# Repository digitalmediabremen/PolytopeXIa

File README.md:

# Polytope XIa

see *developer blog* at https://digitalmediabremen.github.io/PolytopeXIa/

## how to convert a java sketches to processing

navigate to sketch folder ( i.e `./PolytopeXIa/sketches` ) and run shell script `convert-java-to-processing.sh` with the first argument pointing to the java sketch source file:

```
./convert-java-to-processing.sh ../src/de/hfkbremen/polytopexia/sketches/LaserBeamLogo.java
```

note that you might need to manually add libraries in the processing editor ( e.g `import teilchen.*;` or `import.gewebe.*;` ( from https://github.com/dennisppaul/gewebe ) ).

## See osc.schema.md for a list of commands

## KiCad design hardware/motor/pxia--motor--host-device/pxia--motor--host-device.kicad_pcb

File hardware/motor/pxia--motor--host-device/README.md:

# Polytope XIa / hardware / motor / host-device

( TTL>RS485>RJ45 ) 

- via MAX490

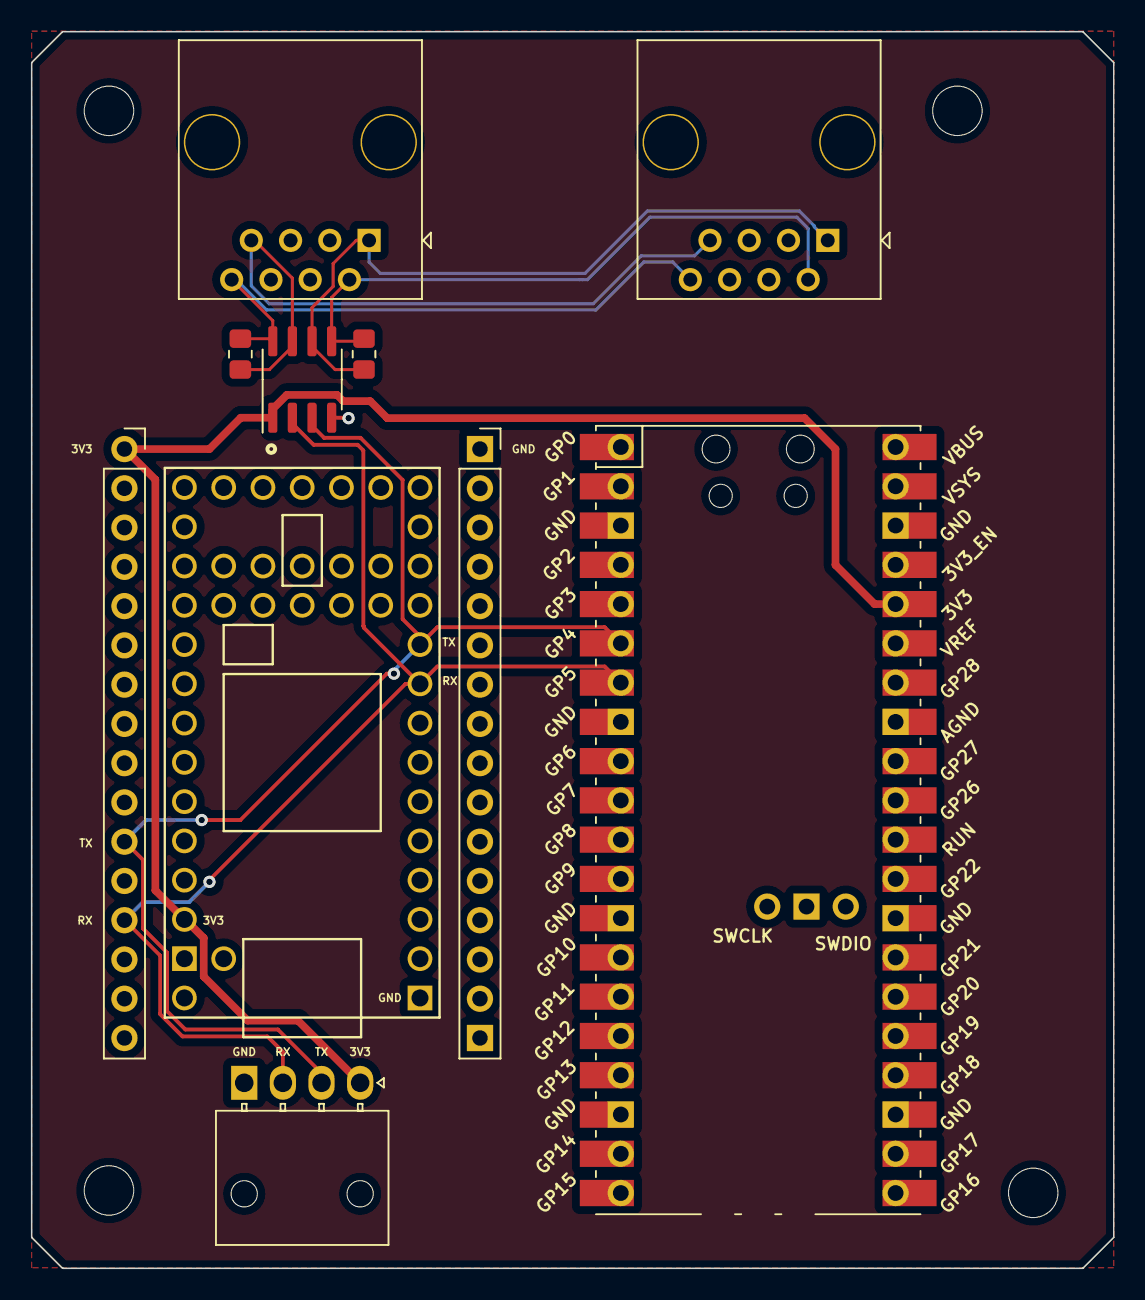
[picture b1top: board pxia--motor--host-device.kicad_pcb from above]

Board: 2 copper layers, 70.0 x 80.0 mm, 14 parts (0 on the bottom side), 8 nets.

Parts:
H1, H2, H3, H4: M3; MountingHole_3.2mm_M3
J1, J5: RJ45; RJ45_OST_PJ012-8P8CX_Vertical
J2: Lolin D32 Pro 2.0.0 (ESP32) PIN17–32; PinSocket_1x16_P2.54mm_Vertical
J3: GENERIC_UART; Molex_Nano-Fit_105313-xx04_1x04_P2.50mm_Horizontal
J4: Lolin D32 Pro 2.0.0 (ESP32) PIN01–16; PinSocket_1x16_P2.54mm_Vertical
R1, R2: 120R; R_0805_2012Metric_Pad1.20x1.40mm_HandSolder
U1: Teensy4.0; Teensy40
U2: max3490eesa+T; SOIC-8_3.9x4.9mm_P1.27mm
U3: PicoW; RPi_PicoW_SMD_TH

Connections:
+3V3: J3.1, J4.1, U1.31 (3V3), U2.1 (VCC), U3.36 (3V3)
/MCU_RX: J3.3, J4.13, U1.9 (7_RX2_OUT1A), U2.2 (RO), U3.7 (GPIO5)
/MCU_TX: J3.2, J4.11, U1.10 (8_TX2_IN1), U2.3 (DI), U3.6 (GPIO4)
/RX+: J1.2, J5.2, R1.1, U2.5 (Y)
/RX-: J1.1, J5.1, R1.2, U2.6 (Z)
/TX+: J1.8, J5.8, R2.1, U2.8 (A)
/TX-: J1.7, J5.7, R2.2, U2.7 (B)
GND: J2.1, J2.16, J3.4, U1.1 (GND), U1.17 (GND), U1.32 (AGND), U2.4 (GND), U3.3 (GND), U3.8 (GND), U3.13 (GND), U3.18 (GND), U3.23 (GND), U3.28 (GND), U3.33 (AGND), U3.38 (GND), U3.42 (GND)

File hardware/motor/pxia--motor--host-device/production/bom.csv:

Designator,Footprint,Quantity,Value,LCSC Part #
"H1, H2, H3, H4",MountingHole_3.2mm_M3,4,M3,DNF
"J1, J5",RJ45_OST_PJ012-8P8CX_Vertical,2,RJ45,C305983
J2,PinSocket_1x16_P2.54mm_Vertical,1,Lolin D32 Pro 2.0.0 (ESP32) PIN17–32,DNF
J3,Molex_Nano-Fit_105313-xx04_1x04_P2.50mm_Horizontal,1,GENERIC_UART,DNF
J4,PinSocket_1x16_P2.54mm_Vertical,1,Lolin D32 Pro 2.0.0 (ESP32) PIN01–16,DNF
"R1, R2",R_0805_2012Metric_Pad1.20x1.40mm_HandSolder,2,120R,C114244
U1,Teensy40,1,Teensy4.0,DNF
U2,SOIC-8_3.9x4.9mm_P1.27mm,1,max3490eesa+T,C23404
U3,RPi_PicoW_SMD_TH,1,PicoW,DNF

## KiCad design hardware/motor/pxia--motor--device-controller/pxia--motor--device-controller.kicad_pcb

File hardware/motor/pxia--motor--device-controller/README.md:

# Polytope XIa / hardware / motor / device-controller

( RJ45+PWR>JSTPHD )

## RJ45 connector @JLCPCB

### horizontal

- MFR.Part # [1-406525-1](https://jlcpcb.com/partdetail/TeConnectivity-1_4065251/C125066)

### vertical

- MFR.Part # [5555799-1](https://jlcpcb.com/partdetail/TeConnectivity-55557991/C305983) #black #plastic #vertical **FAV**
- MFR.Part # [5557969-1](https://jlcpcb.com/partdetail/TeConnectivity-55579691/C305977) #silver #metal #vertical

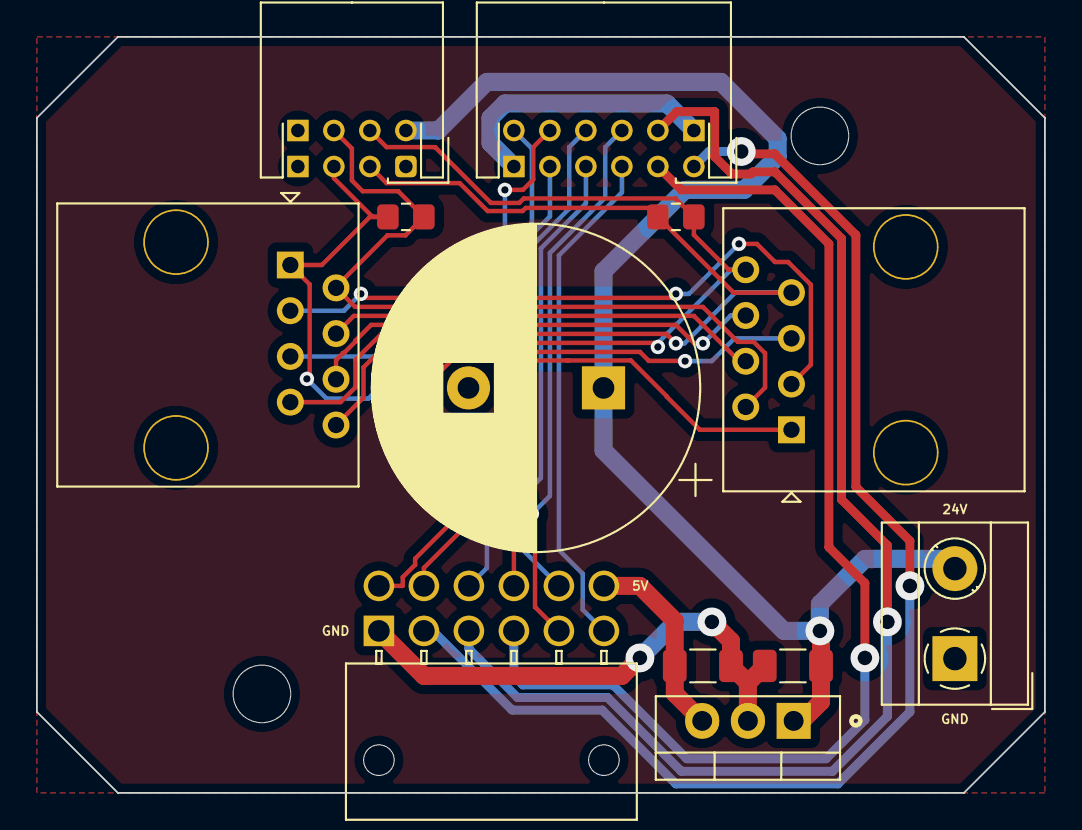
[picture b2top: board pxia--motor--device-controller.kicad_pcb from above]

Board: 2 copper layers, 56.0 x 42.0 mm, 14 parts (0 on the bottom side), 21 nets.

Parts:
C1: 4700uF; CP_Radial_D18.0mm_P7.50mm
C2: 330nF; C_1206_3216Metric_Pad1.33x1.80mm_HandSolder
C3: 100nF; C_1206_3216Metric_Pad1.33x1.80mm_HandSolder
H2, H4: M3; MountingHole_3.2mm_M3
J1: IDC(>ENC); Molex_Nano-Fit_105314-xx12_2x06_P2.50mm_Horizontal
J2: JST-PHD(>SMCI12(X12)); JST_PHD_S8B-PHDSS_2x04_P2.00mm_Horizontal
J3: JST-PHD(>SMCI12(X11)); JST_PHD_S12B-PHDSS_2x06_P2.00mm_Horizontal
J4: PWR_SUPPLY; TerminalBlock_MetzConnect_Type055_RT01502HDWU_1x02_P5.00mm_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
J5, J6: RJ45; RJ45_OST_PJ012-8P8CX_Vertical
R1, R2: 120R; R_0805_2012Metric_Pad1.20x1.40mm_HandSolder
U1: LM7805_TO220; TO-220-3_Vertical

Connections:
+5V: C3.1, J1.1, U1.3 (VO)
+24V: C1.1, C2.2, J2.2, J4.2, U1.1 (VI)
/ANALOG_IN: J1.8, J3.6
/INPUT_1: J1.2, J3.12
/INPUT_2: J1.3, J3.9
/INPUT_3: J1.4, J3.10
/INPUT_4: J1.5, J3.7
/INPUT_5: J1.6, J3.8
/INPUT_6: J1.7, J3.5
/OUTPUT_1: J1.9, J3.3
/OUTPUT_2: J1.10, J3.4
/OUTPUT_3: J1.11, J3.1
/RX+: J2.6, J5.2, J6.2, R1.1
/RX-: J2.5, J5.1, J6.1, R1.2
/TX+: J2.4, J5.8, J6.8, R2.1
/TX-: J2.3, J5.7, J6.7, R2.2
GND: C1.2, C2.1, C3.2, J1.12, J2.1, J2.7, J2.8, J3.2, J3.11, J4.1, U1.2 (GND)
unnamed: J5.3, J6.3
unnamed: J5.4, J6.4
unnamed: J5.5, J6.5
unnamed: J5.6, J6.6

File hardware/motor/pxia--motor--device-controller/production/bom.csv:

Designator,Footprint,Quantity,Value,LCSC Part #
C1,CP_Radial_D18.0mm_P7.50mm,1,4700uF,DNF
C2,C_1206_3216Metric_Pad1.33x1.80mm_HandSolder,1,330nF,C307572
C3,C_1206_3216Metric_Pad1.33x1.80mm_HandSolder,1,100nF,C1945
"H2, H4",MountingHole_3.2mm_M3,2,M3,DNF
J1,Molex_Nano-Fit_105314-xx12_2x06_P2.50mm_Horizontal,1,IDC(>ENC),DNF
J2,JST_PHD_S8B-PHDSS_2x04_P2.00mm_Horizontal,1,JST-PHD(>SMCI12(X12)),DNF
J3,JST_PHD_S12B-PHDSS_2x06_P2.00mm_Horizontal,1,JST-PHD(>SMCI12(X11)),DNF
J4,TerminalBlock_MetzConnect_Type055_RT01502HDWU_1x02_P5.00mm_Horizontal,1,PWR_SUPPLY,
"J5, J6",RJ45_OST_PJ012-8P8CX_Vertical,2,RJ45,
"R1, R2",R_0805_2012Metric_Pad1.20x1.40mm_HandSolder,2,120R,
U1,TO-220-3_Vertical,1,LM7805_TO220,

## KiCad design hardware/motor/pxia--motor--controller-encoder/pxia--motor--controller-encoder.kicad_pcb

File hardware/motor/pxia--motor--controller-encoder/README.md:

# Polytope XIa / hardware / motor / controller-encoder

( JSTPHD>JSTPHD )

## external high power LED

### use as switch transistor/MOSFET

- LM317 [How to use High Power Led with Arduino/low voltage signal.](https://youtu.be/0mYwr933rz8?t=35)
- TIP122:

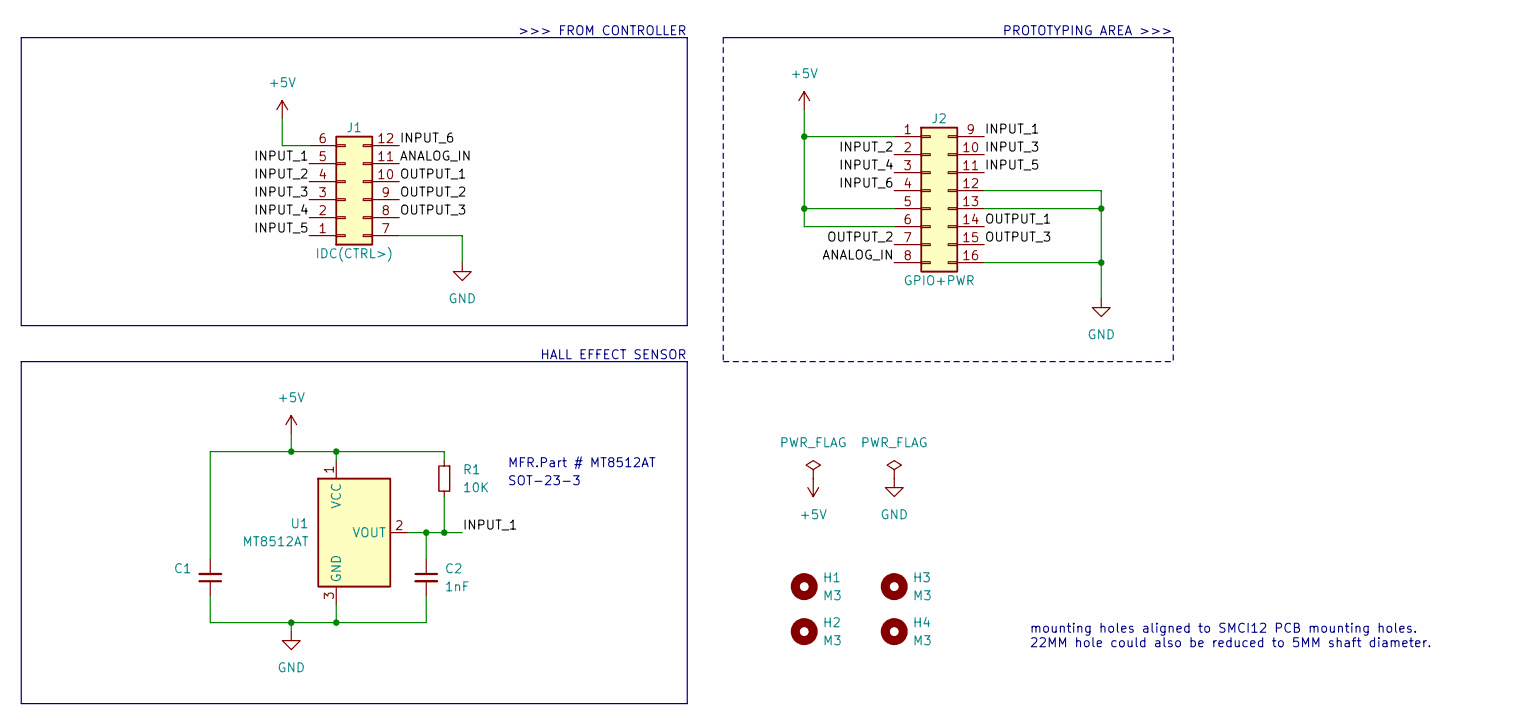
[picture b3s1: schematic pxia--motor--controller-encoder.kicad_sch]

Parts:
C1: LCSC C14663
C2: 1nF; C_0603_1608Metric; LCSC C1588
H1, H2, H3, H4: M3; MountingHole_3.2mm_M3
J1: IDC(CTRL>); Molex_Nano-Fit_105314-xx12_2x06_P2.50mm_Horizontal
J2: GPIO+PWR; Molex_Nano-Fit_105314-xx16_2x08_P2.50mm_Horizontal
R1: 10K; R_0603_1608Metric; LCSC C25804
U1: MT8512AT; SOT-23_Handsoldering; LCSC C879601

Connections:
+5V: C1.2, J1.6, J2.1, J2.5, J2.6, R1.1, U1.1 (VCC)
/ANALOG_IN: J1.11, J2.8
/INPUT_1: C2.1, J1.5, J2.9, R1.2, U1.2 (VOUT)
/INPUT_2: J1.4, J2.2
/INPUT_3: J1.3, J2.10
/INPUT_4: J1.2, J2.3
/INPUT_5: J1.1, J2.11
/INPUT_6: J1.12, J2.4
/OUTPUT_1: J1.10, J2.14
/OUTPUT_2: J1.9, J2.7
/OUTPUT_3: J1.8, J2.15
GND: C1.1, C2.2, J1.7, J2.12, J2.13, J2.16, U1.3 (GND)

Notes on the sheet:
HALL EFFECT SENSOR
MFR.Part # MT8512AT
>>> FROM CONTROLLER
SOT-23-3
mounting holes aligned to SMCI12 PCB mounting holes. 22MM hole could also be reduced to 5MM shaft diameter.
PROTOTYPING AREA >>>

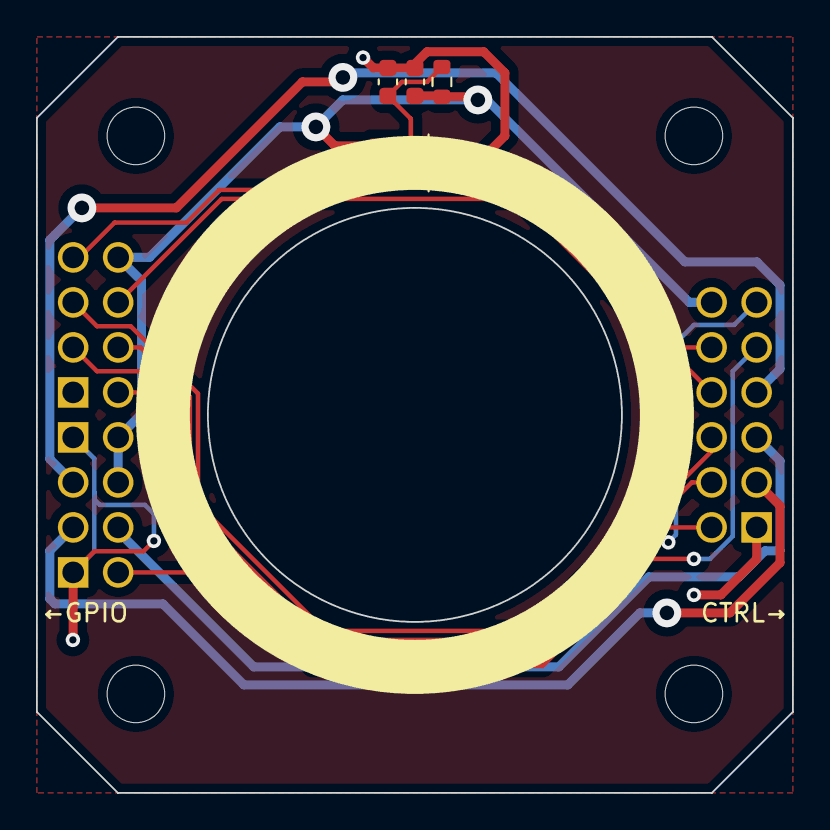
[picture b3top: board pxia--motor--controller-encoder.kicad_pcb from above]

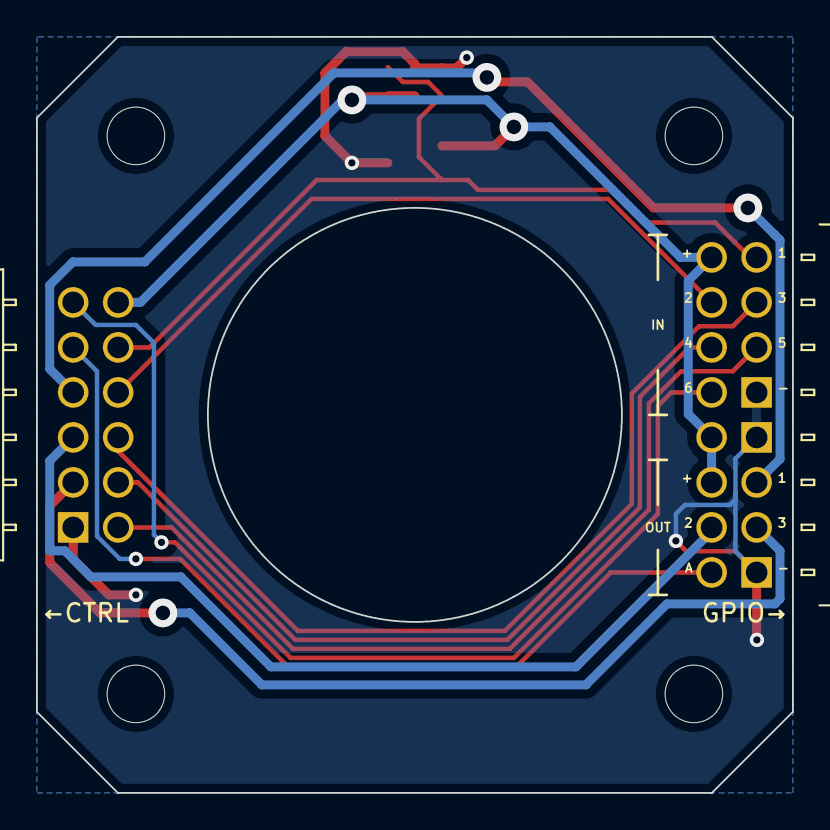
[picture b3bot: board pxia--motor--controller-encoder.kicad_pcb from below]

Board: 2 copper layers, 42.0 x 42.0 mm, 10 parts (2 on the bottom side), 12 nets.

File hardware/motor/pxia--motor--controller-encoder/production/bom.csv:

Designator,Footprint,Quantity,Value,LCSC Part #
C1,C_0603_1608Metric,1,100nF,
C2,C_0603_1608Metric,1,1nF,
"H1, H2, H3, H4",MountingHole_3.2mm_M3,4,M3,
J1,Molex_Nano-Fit_105314-xx12_2x06_P2.50mm_Horizontal,1,IDC(CTRL>),
J2,Molex_Nano-Fit_105314-xx16_2x08_P2.50mm_Horizontal,1,GPIO+PWR,
R1,R_0603_1608Metric,1,10K,
U1,SOT-23_Handsoldering,1,MT8512AT,

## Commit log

2022-04-22 added laser beam logo sketch
2022-04-22 added reflect beam sketch
2022-04-28 minor changes
2022-05-03 added dev diary
2022-05-05 tried fixing website
2022-05-05 added S003
2022-05-05 updated gemfile
2022-05-05 fixing pages
2022-05-05 fixing dev diary
2022-05-05 updated path
2022-05-05 fixed diary
2022-05-05 update URL
2022-05-05 cleaned up
2022-05-05 updated S002
2022-05-19 removed debug information
2022-06-02 added s004
2022-06-02 removed mail
2022-06-03 fixed miro board URL
2022-06-20 added sessions
2022-06-20 updated sketches
2022-07-12 added mirror grid sketch
2022-07-13 improved grid mirror sketch
2022-07-13 updated mirror grid
2022-07-14 added S010
2022-07-14 added 3D view
2022-08-04 added PCB designs, added datasheets, added sketches
2022-08-04 updated schematics + footprint
2022-08-04 updated gitignore
2022-08-16 added drawing, added ESP32 to host board
2022-08-31 finished schematics and most of pcb layout
2022-09-02 updated PCBs
2022-09-02 finished routing
2022-09-03 added PicoW, finished PCB layout
2022-09-05 updated schematics
2022-09-05 resizable window, correct mirror dimensions, adding movingheads with accurate beam angles
2022-09-05 mirrorsketch: fix typo
2022-09-05 mirrorsketch: add janusz styling and agreed layout
2022-09-05 mirrorsketch: add angle placement via drag and drop
2022-09-05 make poles draggable to
2022-09-06 mirrorsketch: improve drag and drop ux
2022-09-06 cleaned up, production ready
2022-09-19 updated PCB and schematics
2022-09-22 updated documentation, fixed wrong wiring
2022-09-22 added simple example
2022-09-27 added PCBs as freecad
2022-09-27 added production files
2022-10-14 added sanity test for stepper motors
2022-10-21 save all
2022-10-21 dont give full final positino tostepper
2022-10-21 bulk
2022-10-22 final version
2022-10-27 add vezer project files
2022-10-27 refactor mc software
